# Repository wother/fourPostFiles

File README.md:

# THIS IS A README

Here are the files for the SAO that I passed out at defcon.

Thank you for reading this document.

As for how this little thing works, there are six resistors that will needed to be added to the board.

## R1 & R4

You Positive, big input from your amp.

## R2 & R3

Your negative, little input from your amp.

## R5

this is for the connection to the grounding plane, it can be bridged (Zero Ohmes Resistor) or you can drop a resistor here to tweak your sound profile.

## R6

This one is for the LED at D1. I was gonna make this blink, in the tradition of all SAO being blinky, but in the OTHER tradition of SAO I got lazy, and just put the pads there.

## Notes

I am probably distributing these with both the standoffs on (with resistors) and standoffs off (no resistors). You can source all the bits from the schematics and KiCad files. Oh, you will need KiCad 6? I think? That is the version I used to make the files, so your milage may vary with other versions of the software.

## Warrenty

This thing comes "as is" with no warrenty, implied or otherwise. Good friggin' luck.

## Final thoughts

If you have questions, comments, or just need someone to yell at, feel free to drop me a line on the email address on the SAO itself. If you think you can do this better, and come up with a modified file, I would LOVE to see it. I used this whole thing to learn the tools involved, and to not have to deal with switching audio interfaces. Again, inspired by laziness.

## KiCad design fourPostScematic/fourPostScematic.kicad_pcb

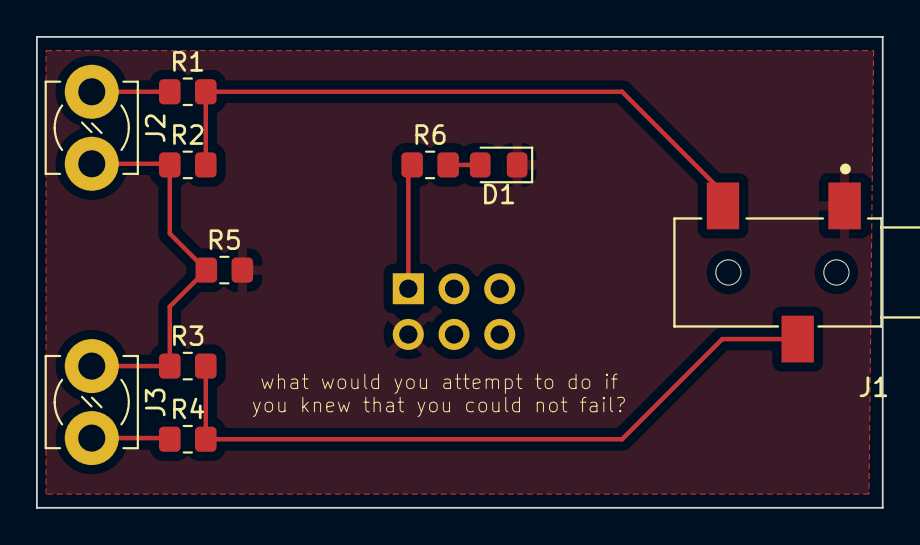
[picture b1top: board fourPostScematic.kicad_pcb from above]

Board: 2 copper layers, 47.0 x 26.2 mm, 11 parts (0 on the bottom side), 8 nets.

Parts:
D1: LED; LED_0805_2012Metric_Pad1.15x1.40mm_HandSolder
J1: SJ2-35813A-SMT-TR; CUI_SJ2-35813A-SMT-TR
J2, J3: Conn_01x02_Male; TerminalBlock_MetzConnect_360381_1x01_Horizontal_ScrewM3.0
R1, R4: 5; R_0805_2012Metric_Pad1.20x1.40mm_HandSolder
R2, R3: 3; R_0805_2012Metric_Pad1.20x1.40mm_HandSolder
R5: 0; R_0805_2012Metric_Pad1.20x1.40mm_HandSolder
R6: 1000; R_0805_2012Metric_Pad1.20x1.40mm_HandSolder
X1: Simple_Addon_v2; Simple_Addon_v2-SAO-2x3

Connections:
+3V3: R6.1, X1.1 (VCC)
GND: D1.1 (K), J1.1, R5.2, X1.2 (GND)
unnamed: D1.2 (A), R6.2
unnamed: J2.1, R1.1
unnamed: J1.2, R1.2, R2.2
unnamed: J2.2 (Pin_1), J3.2 (Pin_1), R2.1, R3.1, R5.1
unnamed: J1.3, R3.2, R4.2
unnamed: J3.1, R4.1

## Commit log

2022-06-29 Here are the base files
2022-07-15 init
